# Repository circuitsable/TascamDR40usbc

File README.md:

# TascamDR40usbc

This is an adapter PCB that replaces the DR-40's USB mini port with a host charging capable USB C port.

# Why/About

I have done USB C mods to many of the devices I own, and I wanted to make one for my DR-40. This may also work on a DR-40X, but I do not own one to confirm this. This may work on any SMD USB mini port, I have used this pcb on several devices that are not the DR-40.

This mod uses 0402 SMD resistors and a small pitched USB C port, so it will require some soldering experience.

# What you'll need

The PCB, of which gerbers are available for in the [releases](https://github.com/circuitsable/TascamDR40usbc/releases/tag/gerbers). It has to be 0.8mm thick to stay within the USB mini's original footprint/volume. The PCB can be ordered from any board house, but some may not like the castellated holes or charge extra for them. **This PCB will most likely violate the anular ring sizes for your board house.** [Oshpark](https://oshpark.com/#services) will do castellated holes, has 0.8mm availability, is quite cheap, and tolerated the anular ring size violations, but the finished boards may require post processing with a small knife.

2 0402 4.7k SMD resistors. They can be sourced from anywhere, here are some examples: [Aliexpress](https://www.aliexpress.us/item/3256801250708458.html), [Ebay](https://www.ebay.com/itm/233161891164), [Mouser](https://www.mouser.com/ProductDetail/Vishay-Dale/CRCW04024K70FKED?qs=Jz%252BxJjKhzTxI08uguE%252B9mA%3D%3D), [Digikey](https://www.digikey.com/en/products/detail/yageo/RC0402FR-074K7L/2827563)

1 GCT 16 Pin 4105 Horizontal SMD USB C Port. They can be sourced from anywhere, here are some examples: [Aliexpress](https://www.aliexpress.us/item/3256806167232408.html), [Ebay](https://www.ebay.com/itm/165653029078), [Mouser](https://www.mouser.com/ProductDetail/GCT/USB4105-GF-A?qs=KUoIvG%2F9IlY%2FMLlBMpStpA%3D%3D), [Digikey](https://www.digikey.com/en/products/detail/gct/USB4105-GF-A/11198441)

Basic soldering equipment.

Hobby knife.

Needle nose pliers.

File/Side cutters (Optional).

# Installation

Disassemble and remove the USB mini port from your DR-40. This can be destructively to the original port (as long as pads are kept intact), or with a hot air station. Use solder wick to make the removed port's pads flat. If your DR-40 has a metalic mesh tape loop ontop of the USB port, keep it safe for later.

Touch up the castellated holes of your PCB with a hobby knife, as they will most certainly arrive with excess material from the pads being drilled. You may also need to file/cut off excess PCB material from its original paneling. 

Seat the USB C port as forward as it will go on the pcb, and solder **only the front two legs** of it to keep it positioned. Next, solder the USB C port's 12 pins to the PCB. Afterwards, solder the two resistors onto their footprints while being careful to not bridge any pins. 

Allign the adapter PCB into the silkscreen of the removed USB Mini port, trying to allign it down the middle as best as possible, as well as leaving as little pad depth as possible. Solder the USB C port's shield to the 4 shield pads onto the DR-40 PCB. Finally, solder the adapter's castellated holes to the old USB data/power lines. 

Double check all of your work for shorts, especially the castellated holes. Touching up shorts tends to move the resistors, so remain patient. Clean up flux residue. If your DR-40 came with a metalic mesh tape piece ontop of it's original USB mini port, place it ontop of the USB C port.

Use pliers to bend a bit of the shielding between the digital and analog board to make room for the USB C port, as shown in the image below.

Remove plastic as shown in the image below from the casing to make room for the USB C port. This can be done neatly with a hobby knife and some files. Reassemble enough to test.

# PCB Images

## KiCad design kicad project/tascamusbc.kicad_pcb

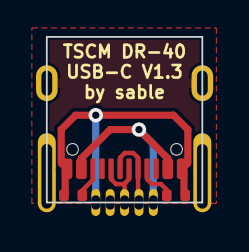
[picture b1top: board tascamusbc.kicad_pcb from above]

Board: 2 copper layers, 8.6 x 9.2 mm, 4 parts (0 on the bottom side), 6 nets.

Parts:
J1: USB_B_Mini; USB_Mini-B_Wuerth_65100516121_Horizontal
J2: USB_C_Receptacle_USB2.0; USB_C_Receptacle_GCT_USB4105-xx-A_16P_TopMnt_Horizontal
R1, R2: 5.1K; R_0402_1005Metric

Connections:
/CC1: J2.A5 (CC1), R1.1
/CC2: J2.B5 (CC2), R2.1
/D+: J1.3 (D+), J2.A6 (D+), J2.B6 (D+)
/D-: J1.2 (D-), J2.A7 (D-), J2.B7 (D-)
/GND: J1.5 (GND), J2.A1 (GND), J2.A12 (GND), J2.B1 (GND), J2.B12 (GND), R1.2, R2.2
/VBUS: J1.1 (VBUS), J2.A4 (VBUS), J2.A9 (VBUS), J2.B4 (VBUS), J2.B9 (VBUS)

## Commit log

2024-04-14 add readme
2024-04-14 add images
2024-04-14 add kicad design files
2024-04-14 add gerbers
2024-04-30 doesnt work :(
2024-04-30 doesnt work ;(
2024-04-30 all images
2024-10-27 found the issue....
2024-10-27 better wording
2024-10-27 updated photos
2024-10-27 new gerbers
2024-10-27 updated project
2024-12-05 updated images
2024-12-05 updated schematic
2025-03-22 2nd try
